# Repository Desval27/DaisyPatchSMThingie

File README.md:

# Prototyping Carrier Board for the Daisy Patch SM™ 

[https://electro-smith.com/products/daisy-seed](https://electro-smith.com/products/patch-submodule)

This PCB is designed to breakout all the PINs of the Daisy Patch Submodule along with additional components such as push buttons, LEDs, potentiometers, I<sup>2</sup>C, and SD card interfaces along with enough room for a typical 830 point breadboard.  

All 40 Patch Submodule PINs are available via the pin headers on the left hand side of the board.  The right hand side contains headers to the various additional components.

[Interactive Bill of Materials (BOM)](hardware/bom/ibom.html)

## Ready to Order Gerber Files
- [Default](hardware/gerber_to_order/DaisyPatchSMThingie_254.0x167.64mm_for_Default.zip)
- [Elecrow](hardware/gerber_to_order/DaisyPatchSMThingie_254.0x167.64mm_for_Elecrow.zip)
- [FusionPCB](hardware/gerber_to_order/DaisyPatchSMThingie_254.0x167.64mm_for_FusionPCB.zip)
- [JLCPCB](hardware/gerber_to_order/DaisyPatchSMThingie_254.0x167.64mm_for_JLCPCB.zip)
- [PCBWay](hardware/gerber_to_order/DaisyPatchSMThingie_254.0x167.64mm_for_PCBWay.zip)

# Revision A

## Notes:
- Push buttons are connected on one side to GND to be used with input pullup GPIO pins.
- Potentiomenters are prewired on on the CW & CCW sides to +5V and GND (note this is different than the Daisy Seed Thingie).
- Audio in/out jacks are directly connected to the Daisy's audio in/out pins.
   + If only the mono audio in jack is used left audio in is normalized to right audio in so that they will both be available for processing by the seed if nothing is connected to right audio in jack.
   + If only the modo audio out jack is used then right audio is summed with it unless something is plugged into the right audio out jack.
- JST connectors are provided to breakout the Audio in/out and MIDI in/out signals to external jacks (1/4" Phono, 5-pin DIN, etc.).
- Jumpers are provided to change the configuration between TRS MIDI-A and TRS MIDI-B.  The default configuration is MIDI-A.  If MIDI-B is desired then the jumpers for MIDI-A need to be cut and those for MIDI-B bridged.

## ⚠️ Disclaimer

This project is provided **"as is"**, without warranty of any kind, express or implied,
including but not limited to the warranties of merchantability, fitness for a
particular purpose, and noninfringement.

This is a DIY electronics project intended for educational and experimental use.
Use at your own risk.

The author assumes **no responsibility or liability** for any damage, injury, or loss
resulting from the use or misuse of this design, including but not limited to:

* Damage to connected equipment (Eurorack modules, power supplies, computers, etc.)
* Incorrect assembly or wiring
* Use with incompatible voltages or signal levels
* Personal injury

### Electrical Safety

This project may interface with:

* ±12V Eurorack power rails
* External control voltages (CV)
* Digital and analog circuitry

Improper handling may result in damage or unsafe conditions.

You are responsible for:

* Verifying all connections before powering the system
* Ensuring correct polarity of power connections
* Confirming voltage ranges and signal compatibility
* Using appropriate protection circuits where necessary

### No Guarantees

Schematics, PCB layouts, and code are provided for reference only.
They may contain errors, omissions, or design flaws.

**Always review and validate the design before building or using it.**

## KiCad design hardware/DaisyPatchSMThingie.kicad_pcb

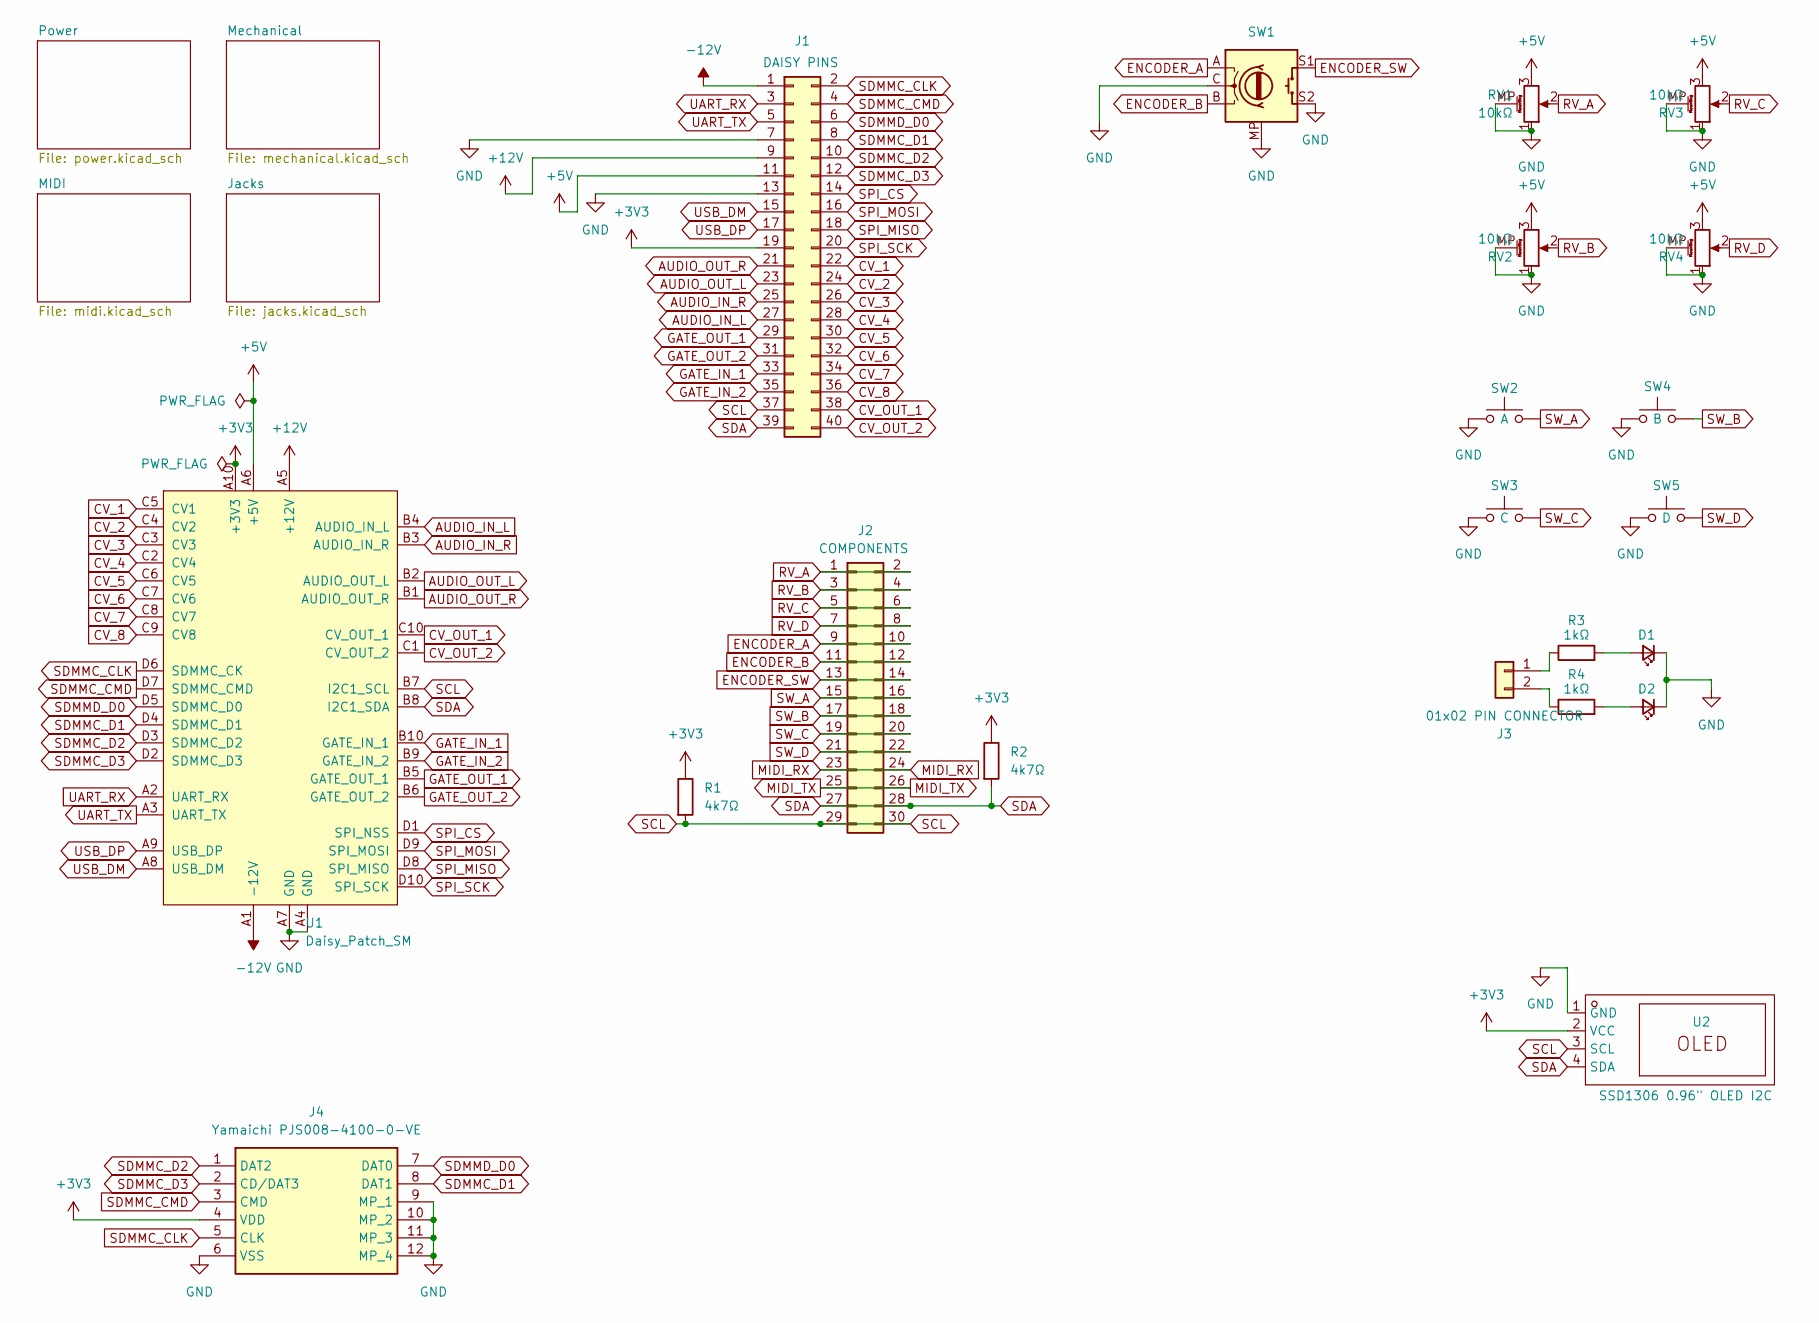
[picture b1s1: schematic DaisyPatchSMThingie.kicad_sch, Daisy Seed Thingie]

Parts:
D1, D2: RED; LED_D5.0mm_FlatTop
J1: Conn_02x20_Odd_Even; PinHeader_2x20_P2.54mm_Vertical
J2: 02x15 PIN CONNECTOR; PinHeader_2x15_P2.54mm_Vertical
J3: 01x02 PIN CONNECTOR; PinHeader_1x02_P2.54mm_Vertical
J4: Yamaichi PJS008-4100-0-VE; Yamaichi PJS00841000VE; Mouser Part Number 945-PJS008-4100-0-VE
R1, R2: 4k7Ω; R_Axial_DIN0204_L3.6mm_D1.6mm_P7.62mm_Horizontal
R3, R4: 1kΩ; R_Axial_DIN0204_L3.6mm_D1.6mm_P7.62mm_Horizontal
RV1, RV2, RV3, RV4: 10kΩ; Potentiometer_Alps_RK09K_Single_Vertical
SW1: EN11C; Rotary Encoder
SW2, SW3, SW4, SW5: SW_PUSH_6mm
U1: Daisy_Patch_SM; DAISY_PATCH_SM
U2: SSD1306 0.96" OLED I2C; 0.96 Inch OLED I2C Display Module; Manufacturer Part HS13L03B2C01; LCSC Part Name 1.3'1.3寸 128*64 OLED显示屏 I2C通讯 SH1106 蓝光

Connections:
+12V: J1.9, U1.A5 (+12V); also elsewhere on the board
-12V: J1.1, U1.A1 (-12V); also elsewhere on the board
AUDIO_IN_L: J1.27, U1.B4 (AUDIO_IN_L); also elsewhere on the board
AUDIO_IN_R: J1.25, U1.B3 (AUDIO_IN_R); also elsewhere on the board
AUDIO_OUT_L: J1.23, U1.B2 (AUDIO_OUT_L); also elsewhere on the board
AUDIO_OUT_R: J1.21, U1.B1 (AUDIO_OUT_R); also elsewhere on the board
CV_1: J1.22, U1.C5 (CV1); also elsewhere on the board
CV_2: J1.24, U1.C4 (CV2); also elsewhere on the board
CV_3: J1.26, U1.C3 (CV3); also elsewhere on the board
CV_4: J1.28, U1.C2 (CV4); also elsewhere on the board
CV_5: J1.30, U1.C6 (CV5); also elsewhere on the board
CV_6: J1.32, U1.C7 (CV6); also elsewhere on the board
CV_7: J1.34, U1.C8 (CV7); also elsewhere on the board
CV_8: J1.36, U1.C9 (CV8); also elsewhere on the board
CV_OUT_1: J1.38, U1.C10 (CV_OUT_1); also elsewhere on the board
CV_OUT_2: J1.40, U1.C1 (CV_OUT_2); also elsewhere on the board
ENCODER_A: J2.9, J2.10, SW1.A
ENCODER_B: J2.11, J2.12, SW1.B
ENCODER_SW: J2.13, J2.14, SW1.S1
GATE_IN_1: J1.33, U1.B10 (GATE_IN_1); also elsewhere on the board
GATE_IN_2: J1.35, U1.B9 (GATE_IN_2); also elsewhere on the board
GATE_OUT_1: J1.29, U1.B5 (GATE_OUT_1); also elsewhere on the board
GATE_OUT_2: J1.31, U1.B6 (GATE_OUT_2); also elsewhere on the board
GND: D1.1 (K), D2.1 (K), J1.7, J1.13, J4.6 (VSS), J4.9 (MP_1), J4.10 (MP_2), J4.11 (MP_3), J4.12 (MP_4), RV1.1, RV1.MP (MountPin), RV2.1, RV2.MP (MountPin), RV3.1, RV3.MP (MountPin), RV4.1, RV4.MP (MountPin), SW1.C, SW1.MP, SW1.S2, SW2.1, SW3.1, SW4.1, SW5.1, U1.A4 (GND), U1.A7 (GND), U2.1 (GND); also elsewhere on the board
MIDI_RX: J2.23, J2.24; also elsewhere on the board
MIDI_TX: J2.25, J2.26; also elsewhere on the board
unnamed: D1.2 (A), R3.2
unnamed: D2.2 (A), R4.2
unnamed: J3.1, R3.1
unnamed: J3.2, R4.1
RV_A: J2.1, J2.2, RV1.2
RV_B: J2.3, J2.4, RV2.2
RV_C: J2.5, J2.6, RV3.2
RV_D: J2.7, J2.8, RV4.2
SCL: J1.37, J2.29, J2.30, R1.2, U1.B7 (I2C1_SCL), U2.3 (SCL)
SDA: J1.39, J2.27, J2.28, R2.2, U1.B8 (I2C1_SDA), U2.4 (SDA)
SDMMC_CLK: J1.2, J4.5 (CLK), U1.D6 (SDMMC_CK)
SDMMC_CMD: J1.4, J4.3 (CMD), U1.D7 (SDMMC_CMD)
SDMMC_D1: J1.8, J4.8 (DAT1), U1.D4 (SDMMC_D1)
SDMMC_D2: J1.10, J4.1 (DAT2), U1.D3 (SDMMC_D2)
SDMMC_D3: J1.12, J4.2 (CD/DAT3), U1.D2 (SDMMC_D3)
SDMMD_D0: J1.6, J4.7 (DAT0), U1.D5 (SDMMC_D0)
SPI_CS: J1.14, U1.D1 (SPI_NSS)
SPI_MISO: J1.18, U1.D8 (SPI_MISO)
SPI_MOSI: J1.16, U1.D9 (SPI_MOSI)
SPI_SCK: J1.20, U1.D10 (SPI_SCK)
SW_A: J2.15, J2.16, SW2.2
SW_B: J2.17, J2.18, SW4.2
SW_C: J2.19, J2.20, SW3.2
SW_D: J2.21, J2.22, SW5.2
UART_RX: J1.3, U1.A2 (UART_RX)
UART_TX: J1.5, U1.A3 (UART_TX)
USB_DM: J1.15, U1.A8 (USB_DM)
USB_DP: J1.17, U1.A9 (USB_DP)

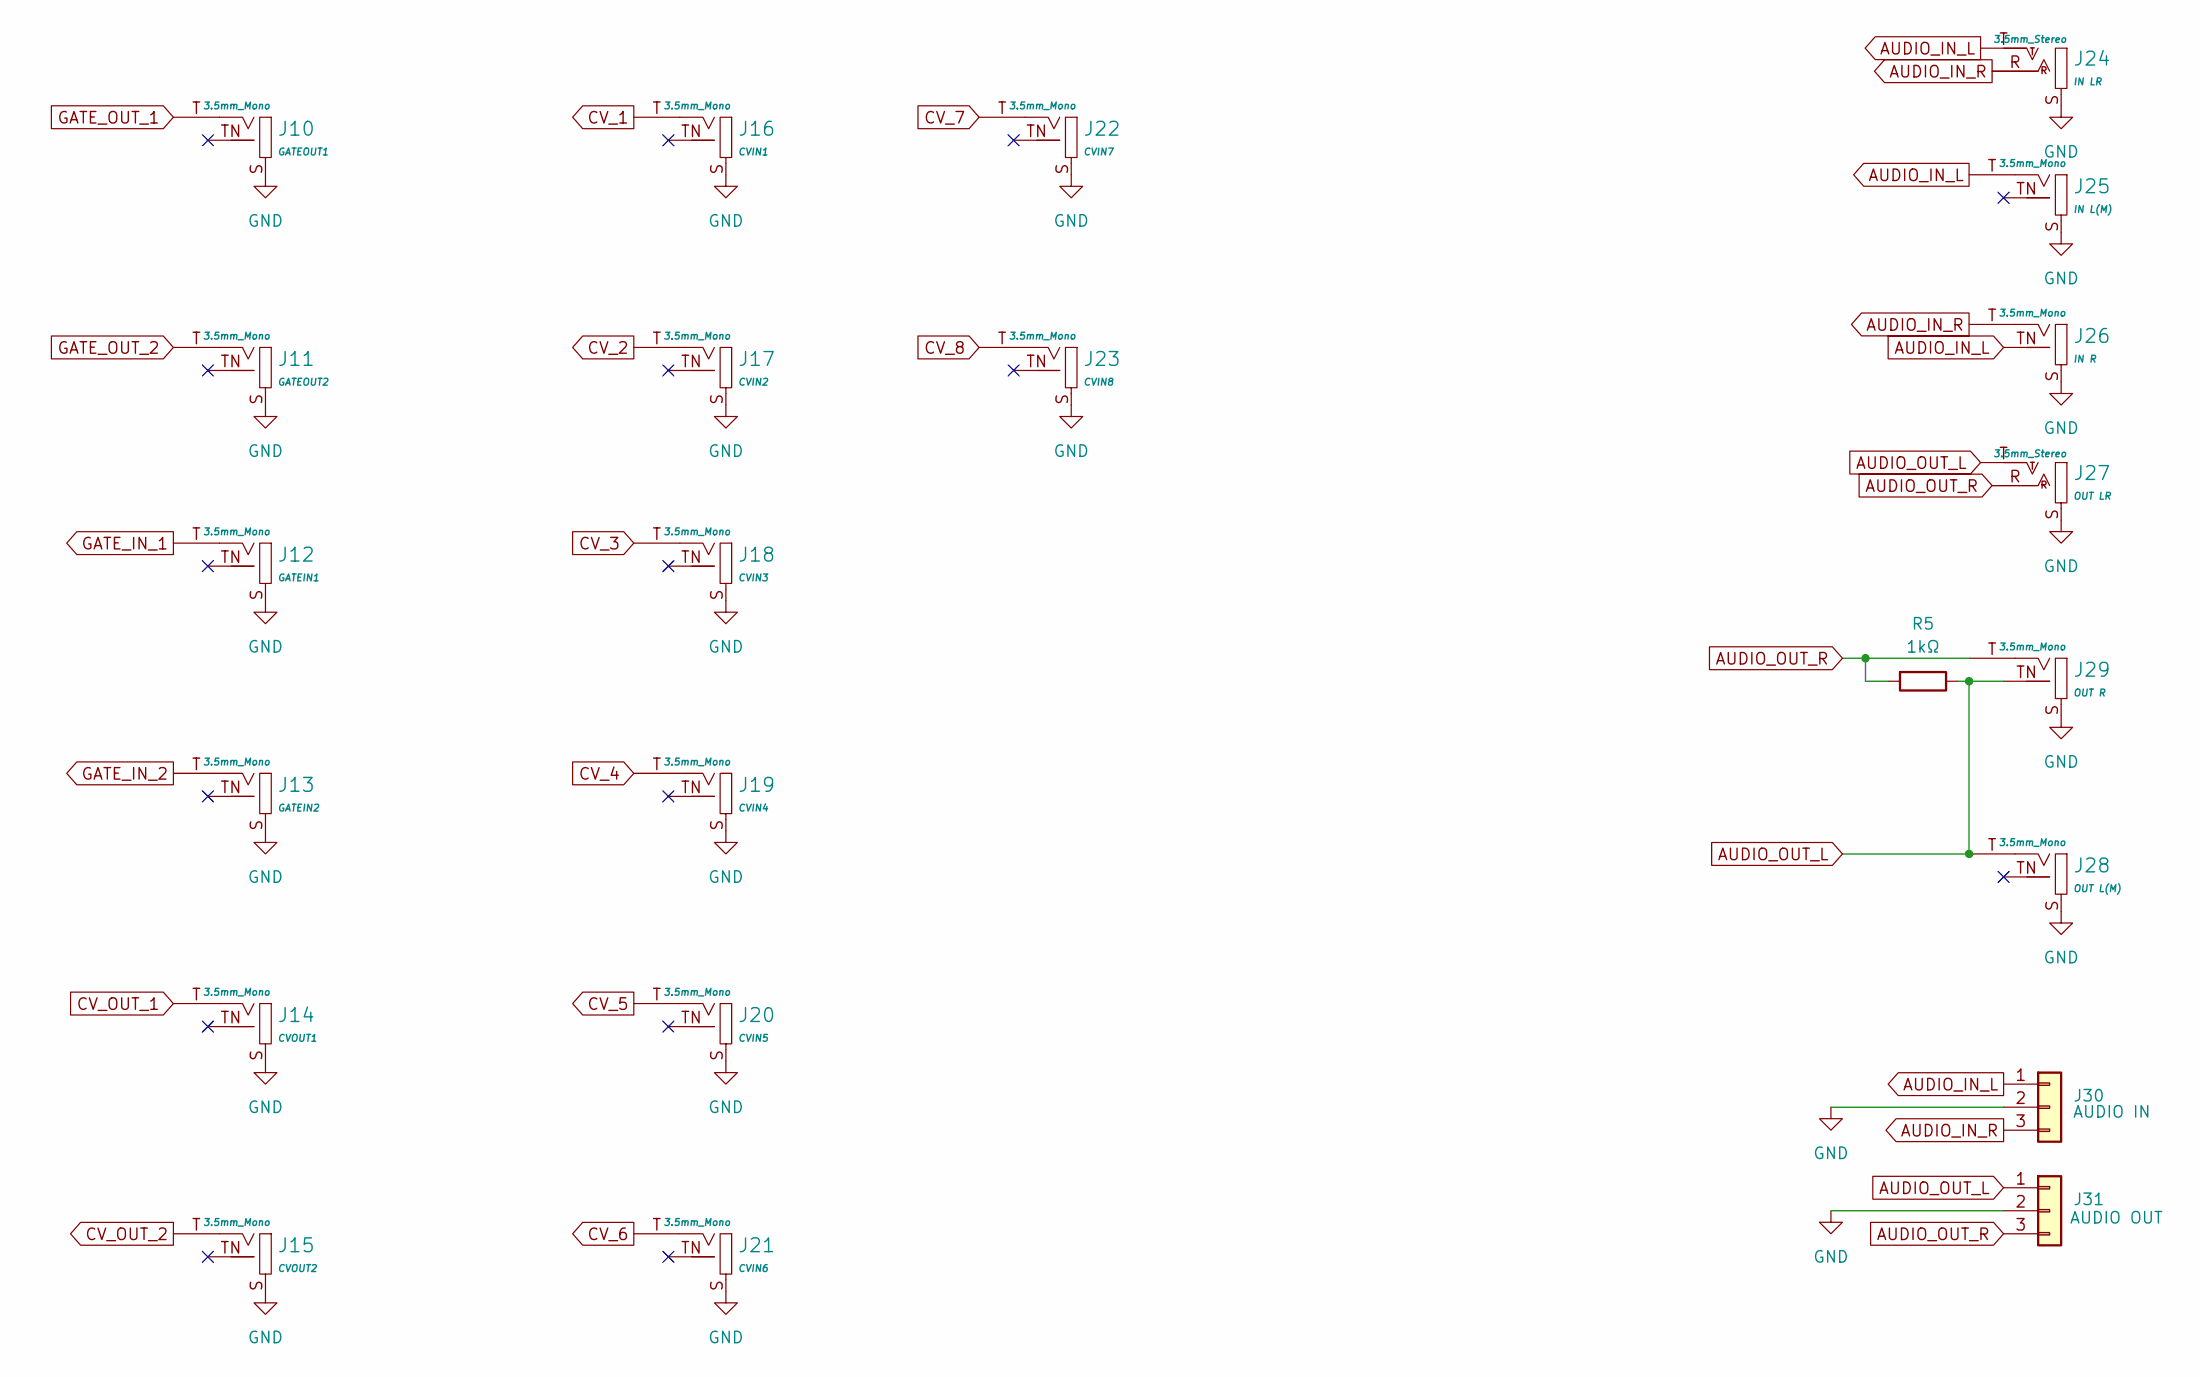
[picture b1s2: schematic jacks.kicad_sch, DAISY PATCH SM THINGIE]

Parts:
J10, J11, J12, J13, J14, J15, J16, J17, J18, J19, J20, J21, J22, J23, J25, J26, J28, J29: MONO 3.5mm; Jack_3.5mm_QingPu_WQP-PJ398SM_Vertical; Part Number WQP-WQP518MA
J24, J27: STEREO 3.5mm; Jack_3.5mm_QingPu_WQP-PJ366ST_Vertical; Part Number WQP-WQP419GR
J30, J31: JST 01x03; JST_XH_B3B-XH-A_1x03_P2.50mm_Vertical
R5: 1kΩ; R_Axial_DIN0204_L3.6mm_D1.6mm_P7.62mm_Horizontal

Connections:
AUDIO_IN_L: J24.T (SIG), J25.T (SIG), J26.TN (SW), J30.1; also elsewhere on the board
AUDIO_IN_R: J24.R (SW), J26.T (SIG), J30.3; also elsewhere on the board
AUDIO_OUT_L: J27.T (SIG), J28.T (SIG), J29.TN (SW), J31.1, R5.1; also elsewhere on the board
AUDIO_OUT_R: J27.R (SW), J29.T (SIG), J31.3, R5.2; also elsewhere on the board
CV_1: J16.T (SIG); also elsewhere on the board
CV_2: J17.T (SIG); also elsewhere on the board
CV_3: J18.T (SIG); also elsewhere on the board
CV_4: J19.T (SIG); also elsewhere on the board
CV_5: J20.T (SIG); also elsewhere on the board
CV_6: J21.T (SIG); also elsewhere on the board
CV_7: J22.T (SIG); also elsewhere on the board
CV_8: J23.T (SIG); also elsewhere on the board
CV_OUT_1: J14.T (SIG); also elsewhere on the board
CV_OUT_2: J15.T (SIG); also elsewhere on the board
GATE_IN_1: J12.T (SIG); also elsewhere on the board
GATE_IN_2: J13.T (SIG); also elsewhere on the board
GATE_OUT_1: J10.T (SIG); also elsewhere on the board
GATE_OUT_2: J11.T (SIG); also elsewhere on the board
GND: J10.S (SHEILD), J11.S (SHEILD), J12.S (SHEILD), J13.S (SHEILD), J14.S (SHEILD), J15.S (SHEILD), J16.S (SHEILD), J17.S (SHEILD), J18.S (SHEILD), J19.S (SHEILD), J20.S (SHEILD), J21.S (SHEILD), J22.S (SHEILD), J23.S (SHEILD), J24.S (SHEILD), J25.S (SHEILD), J26.S (SHEILD), J27.S (SHEILD), J28.S (SHEILD), J29.S (SHEILD), J30.2, J31.2; also elsewhere on the board

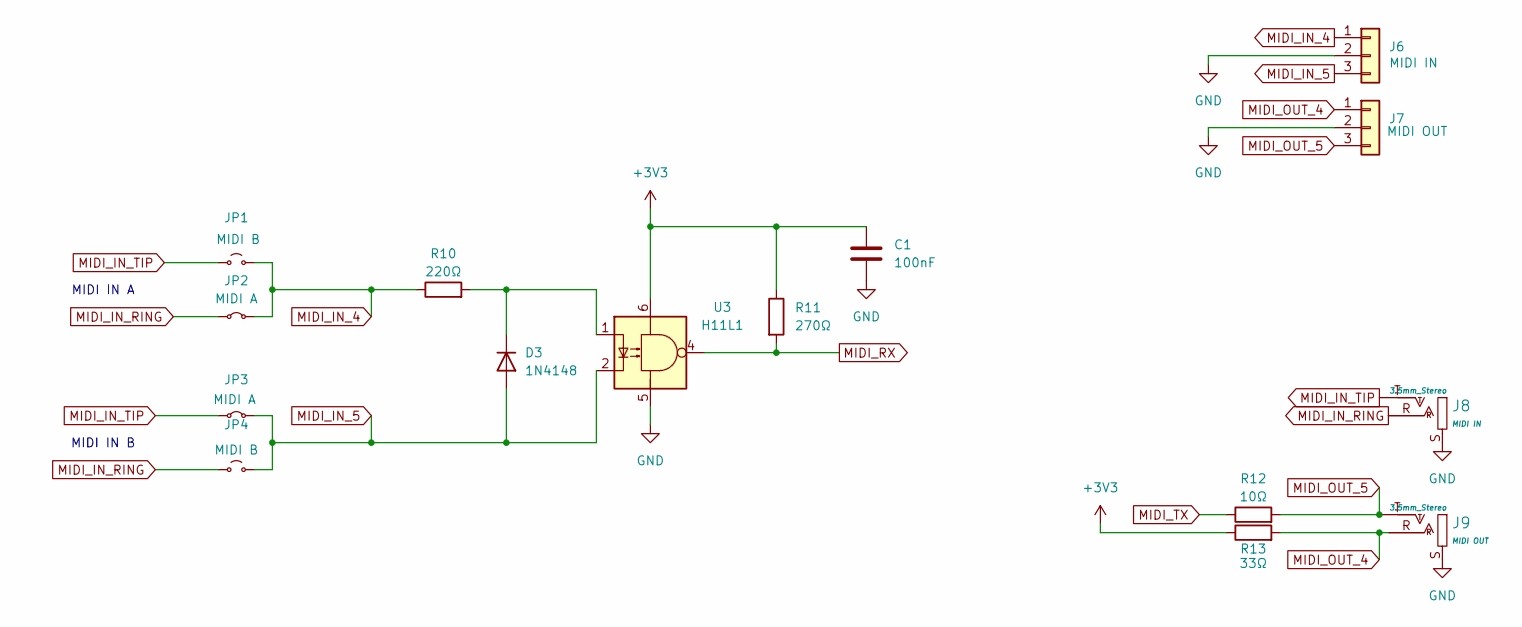
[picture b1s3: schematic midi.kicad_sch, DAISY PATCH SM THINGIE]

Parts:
C1: 100nF; C_Disc_D4.3mm_W1.9mm_P5.00mm
D3: 1N4148; D_DO-35_SOD27_P7.62mm_Horizontal
J6, J7: JST 01x03; JST_XH_B3B-XH-A_1x03_P2.50mm_Vertical
J8, J9: STEREO 3.5mm; Jack_3.5mm_QingPu_WQP-PJ366ST_Vertical; Part Number WQP-WQP419GR
JP1, JP4: JUMPER; Jumper_2_PTH_SMD_Combo-NO
JP2, JP3: JUMPER; Jumper_2_PTH_SMD_Combo-NC
R10: 220Ω; R_Axial_DIN0204_L3.6mm_D1.6mm_P7.62mm_Horizontal
R11: 270Ω; R_Axial_DIN0204_L3.6mm_D1.6mm_P7.62mm_Horizontal
R12: 10Ω; R_Axial_DIN0204_L3.6mm_D1.6mm_P7.62mm_Horizontal
R13: 33Ω; R_Axial_DIN0204_L3.6mm_D1.6mm_P7.62mm_Horizontal
U3: H11L1; DIP-6_W7.62mm_Socket_LongPads

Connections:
GND: C1.2, J6.2, J7.2, J8.S (SHEILD), J9.S (SHEILD), U3.5; also elsewhere on the board
MIDI_IN_4: J6.1, JP1.2 (B), JP2.2 (B), R10.1
MIDI_IN_5: D3.2 (A), J6.3, JP3.2 (B), JP4.2 (B), U3.2
MIDI_IN_RING: J8.R (SW), JP2.1 (A), JP4.1 (A)
MIDI_IN_TIP: J8.T (SIG), JP1.1 (A), JP3.1 (A)
MIDI_OUT_4: J7.1, J9.R (SW), R13.2
MIDI_OUT_5: J7.3, J9.T (SIG), R12.2
MIDI_RX: R11.2, U3.4; also elsewhere on the board
MIDI_TX: R12.1; also elsewhere on the board
unnamed: D3.1 (K), R10.2, U3.1

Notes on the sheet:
MIDI IN B
MIDI IN A

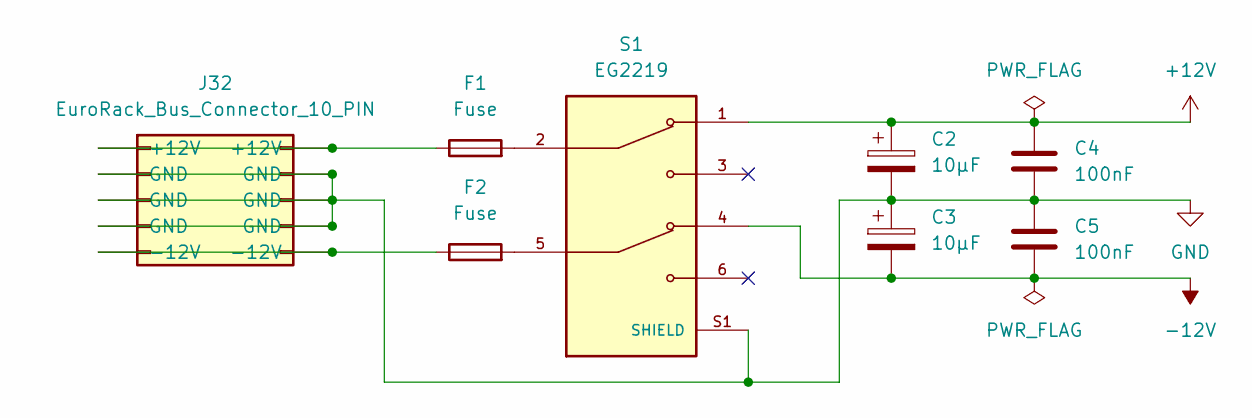
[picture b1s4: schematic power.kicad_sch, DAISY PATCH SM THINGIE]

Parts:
C2, C3: 10µF; CP_Radial_D5.0mm_P2.00mm
C4, C5: 100nF; C_Disc_D4.3mm_W1.9mm_P5.00mm
F1, F2: Fuse; 65600001409
J32: EuroRack_Bus_Connector_10_PIN; IDC-Header_2x05_P2.54mm_Vertical
S1: EG2219; SW_EG2219; PARTREV B

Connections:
+12V: C2.1, C4.1, S1.1; also elsewhere on the board
-12V: C3.2, C5.2, S1.4; also elsewhere on the board
GND: C2.2, C3.1, C4.2, C5.1, J32.3 (GND), J32.4 (GND), J32.5 (GND), J32.6 (GND), J32.7 (GND), J32.8 (GND), S1.S1 (SHIELD), S1.S2 (SHIELD), S1.S3 (SHIELD), S1.S4 (SHIELD); also elsewhere on the board
unnamed: F1.1, J32.9 (+12V), J32.10 (+12V)
unnamed: F1.2, S1.2
unnamed: F2.1, J32.1 (-12V), J32.2 (-12V)
unnamed: F2.2, S1.5

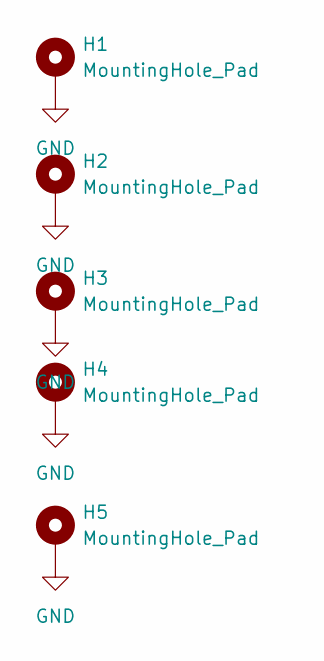
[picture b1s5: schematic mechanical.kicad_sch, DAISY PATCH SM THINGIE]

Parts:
H1, H2, H3, H4, H5: MountingHole_Pad; MountingHole_3.2mm_M3_Pad

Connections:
GND: H1.1, H2.1, H3.1, H4.1, H5.1; also elsewhere on the board

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
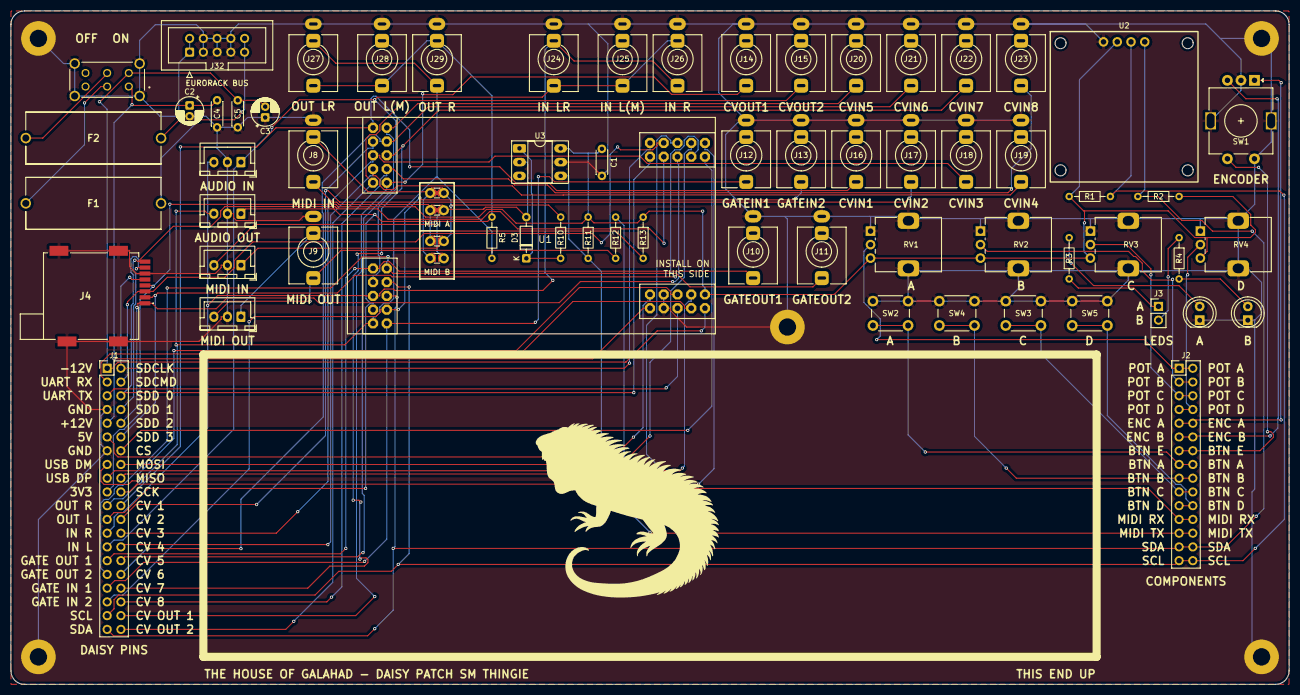
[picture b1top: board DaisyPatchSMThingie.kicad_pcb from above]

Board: 2 copper layers, 236.2 x 124.5 mm, 72 parts (0 on the bottom side), 67 nets.

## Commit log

2026-04-07 Add WIP note to README
2026-04-09 Initial Revision A
2026-04-09 Enhance README with project details and safety warnings
    Added detailed project description, notes, disclaimer, and safety information to README.
2026-04-09 Fix BOM link and clarify audio jack notes
    Updated the link to the Interactive Bill of Materials and revised the audio jack notes for clarity.
2026-04-20 Added Gerber to Order
2026-04-20 Fixed markdown
2026-04-29 Add MIT License to the project
